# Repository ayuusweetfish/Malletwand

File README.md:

# Malletwand: the Pendulum as a Handheld Interface to Musical Timing

**Malletwand** is a handheld controller device in the form of a pendulum (a handle with a swinging bob), which can act as an input interface to the timing of musical playback.

We present this at [NIME](https://nime.org/) 2024 as a short paper ([PDF](paper/nime/paper.pdf); video to-be-updated) in paper session 10, on Friday, 6 Sep.

## Contents

The following directories contain all the files for design and implementation (hardware, firmware, and mechanical).
- **wand/**: the handheld controller (the "Wand").
  - Hardware is a single PCB; firmware for the two controllers are in subdirectories **fw/** (the main one) and **fw_bob/** (the small one in the bob/ball) respectively.
- **mallet/**: one unit of the self-playing (robotic) glockenspiel instrument (the "Mallet").
- **mallet_central/**: the central unit for the instrument, mostly managing communications (both wireless and wired).

To use the files, the following software packages are required (versions for reference):
- Hardware: KiCad (7.0.10)
- Firmware: Arm GNU Toolchain (GCC 10.3.1), STM32Cube ('G0 1.5.0, 'L0 1.12.1), PlatformIO (6.1.15)
- Mechanical: FreeCAD (0.21.1), OpenSCAD (2021.01)

The following directories contain miscellaneous resources:
- **numerical/**: Numerical experiments for the filtering algorithms (EKF and ALS), implemented in Julia.
- **paper/nime/**: The paper's LaTeX source and images.
- **testdrive/**: A testbed prototype for the sensors, created in the early days of development. Includes both hardware and firmware, and a desktop client to receive the BLE signals. Currently not well documented, but might be relevant for inspection (and visualisation?).
- **releases/**: Gerber files submitted to the PCB fabrication house.

## Licence
All content in this repository is distributed under CERN-OHL-S (CERN Open Hardware Licence Version 2, Strongly Reciprocal). See full text at **COPYING.txt** or [online](https://ohwr.org/cern_ohl_s_v2.txt).

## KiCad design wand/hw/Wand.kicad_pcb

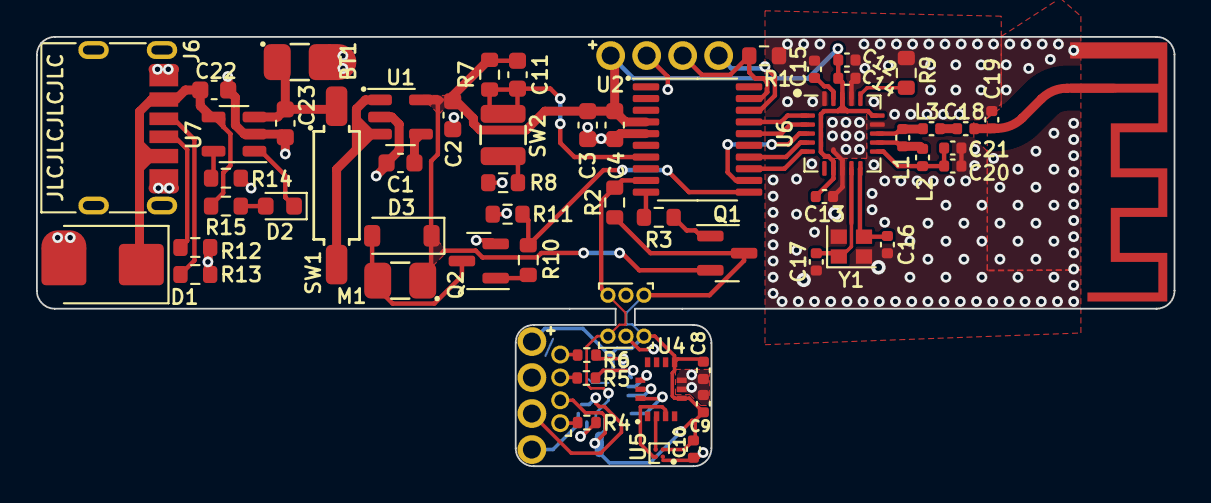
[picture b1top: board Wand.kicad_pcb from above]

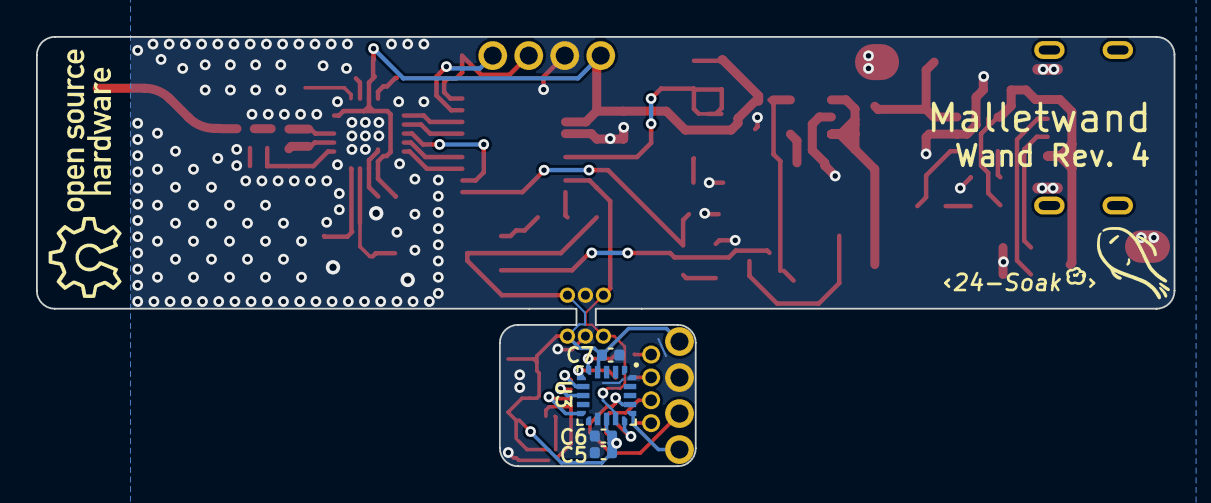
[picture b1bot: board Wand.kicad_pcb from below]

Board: 2 copper layers, 63.2 x 23.8 mm, 65 parts (4 on the bottom side), 49 nets.

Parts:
AE1: 2.4GHz 50R; ANT_IFA_USB_2.4GHz_50R
BT1: LiPo; Pads_1x02_P2.5
C1: 10n; C_0603_1608Metric
C2, C3, C22: 4.7u; C_0603_1608Metric
C4: 100n; C_0603_1608Metric
C5: 10u; C_0402_1005Metric
C6, C7, C8, C9: 100n; C_0402_1005Metric
C10: 2.2u; C_0402_1005Metric
C11: 1n; C_0603_1608Metric
C12: 4.7u; C_0402_1005Metric
C13, C14: 10n; C_0402_1005Metric
C15: 33n; C_0402_1005Metric
C16, C17: 10p; C_0402_1005Metric
C18: 1.5p; C_0402_1005Metric
C19: 1p; C_0402_1005Metric
C20: 2.2n; C_0402_1005Metric
C21: 4.7p; C_0402_1005Metric
C23: 10u; C_0603_1608Metric
D1: SMBJ5.0A; D_SMB
D2: LED; LED_0603_1608Metric
D3: MBR0530; D_SOD-123
J1, J4: Conn_01x04; TestPoints_1x04_P2.0
J2, J3: Conn_01x03; PinHeader_1x03_P1.00mm_Vertical
J5: Conn_01x04; PinHeader_1x04_P1.27mm_Vertical
J6: USB_C_Receptacle_PowerOnly_6P; USB_C_Receptacle
L1: 8.2n; C_0402_1005Metric
L2: 2.7n; C_0402_1005Metric
L3: 3.9n; C_0402_1005Metric
M1: Vib; Pads_1x02_P2.5
Q1: Si2301; SOT-23
Q2: Si2302; SOT-23
R1: 1.2M; R_0603_1608Metric
R2, R3, R10: 1k; R_0603_1608Metric
R4, R5, R6: 2k TBD; R_0402_1005Metric
R7: 3.3M; R_0603_1608Metric
R8, R11: 100k; R_0603_1608Metric
R9: 22k; R_0603_1608Metric
R12, R13: 5.1k; R_0603_1608Metric
R14: 2k; R_0603_1608Metric
R15: 6.8k; R_0603_1608Metric
SW1: SW_SPST; SPST_1x01_P2.54
SW2: Vib; VibSwitch_JYX-1210-X160
U1: SPX3819M5-L-3-3; SOT-23-5
U2: STM32G030F6Px; TSSOP-20_4.4x6.5mm_P0.65mm
U3: STM32L011F4Ux; ST_UFQFPN-20_3x3mm_P0.5mm
U4: BMI270; QFN50P300X250X87-14N
U5: MMC5603NJ; WLP-4_0.86x0.86mm_P0.4mm
U6: nRF24L01P; QFN-20-P0.5
U7: LTC4054ES5-4.2; TSOT-23-5
Y1: 16MHz; Crystal_SMD_2016-4Pin_2.0x1.6mm

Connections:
BMI_CS: U3.7 (PA4), U4.12 (CSB)
BMI_MOSI: U3.10 (PA7), U4.14 (SDX)
BMI_SCK: U3.8 (PA5), U4.13 (SCX)
BOB_DA: J2.3, J3.3, R2.1, U2.9 (PA2), U3.14 (PA9)
BSWCLK: J4.3, U3.17 (PA14)
BSWDIO: J4.4, U3.16 (PA13)
GND: AE1.2, BT1.2 (-), C1.2, C2.2, C3.2, C4.2, C5.2, C6.2, C7.2, C8.2, C9.2, C10.1, C12.2, C13.2, C14.2, C15.2, C16.2, C17.2, C19.2, C20.2, C21.2, C22.2, C23.2, D1.2 (A2), J1.2, J2.2, J3.2, J4.2, J6.A12 (GND), J6.B12 (GND), Q2.2 (S), R1.2, R8.1, R9.2, R11.1, R12.2, R13.2, R14.2, U1.2 (GND), U2.5 (VSS), U3.12 (VSS), U3.20 (PB9), U4.6 (GNDIO), U4.7 (GND), U5.A1 (VSA), U6.8 (VSS), U6.14 (VSS), U6.17 (VSS), U6.20 (VSS), U7.2 (GND), Y1.2, Y1.4
HSWCLK: J1.3, R1.1, U2.19 (PA14/PA15)
HSWDIO: J1.4, U2.18 (PA13)
LED_B: R6.2, U3.5 (PA0)
LED_G: R5.2, U3.6 (PA1)
LED_R: R4.2, U3.15 (PA10)
MOTOR_G: R10.1, R11.2, U2.11 (PA4)
unnamed: AE1.1, C18.2, C19.1
unnamed: C18.1, L3.2
unnamed: D2.2 (A), R15.2
unnamed: D2.1 (K), U7.1 (~CHRG)
unnamed: D3.2 (A), M1.2 (-), Q2.3 (D)
unnamed: J5.1, R4.1
unnamed: J5.3, R5.1
unnamed: J5.4, R6.1
unnamed: J6.A5 (CC1), R13.1
unnamed: J6.B5 (CC2), R12.1
unnamed: Q1.1 (G), R3.2
unnamed: Q2.1 (G), R10.2
unnamed: R8.2, SW2.1
unnamed: SW1.2 (B), U1.1 (IN), U1.3 (EN)
unnamed: C1.1, U1.4 (BP)
unnamed: U4.3 (ASCX), U5.A2 (SCL)
unnamed: U4.2 (ASDX), U5.B2 (SDA)
unnamed: L1.1, L2.1, U6.12 (ANT1)
unnamed: L1.2, L3.1, U6.13 (ANT2)
unnamed: C15.1, U6.19 (DVDD)
unnamed: R9.1, U6.16 (IREF)
unnamed: C20.1, C21.1, L2.2, U6.11 (VDD_PA)
unnamed: C16.1, U6.10 (XC1), Y1.3
unnamed: C17.1, U6.9 (XC2), Y1.1
unnamed: R14.1, U7.5 (PROG)
SUB_VDD_G: R3.1, U2.10 (PA3)
VBAT: BT1.1 (+), C23.1, SW1.1 (A), U7.3 (BAT)
VBUS: C22.1, D1.1 (A1), J6.A9 (VBUS), J6.B9 (VBUS), R15.1, U7.4 (V_{CC})
VDD: C2.1, C3.1, C4.1, C11.1, C12.1, C13.1, C14.1, D3.1 (K), J1.1, M1.1 (+), Q1.2 (S), R7.2, U1.5 (OUT), U2.4 (VDD), U6.7 (VDD), U6.15 (VDD), U6.18 (VDD)
VDDSUB: C5.1, C6.1, C7.1, C8.1, C9.1, C10.2, J2.1, J3.1, J4.1, J5.2, Q1.3 (D), R2.2, U3.4 (VDDA), U3.13 (VDD), U4.5 (VDDIO), U4.8 (VDD), U5.B1 (VDD)
VIB_TRG: C11.2, R7.1, SW2.2, U2.7 (PA0)
nRF_CE: U2.17 (PA12/PA10), U6.1 (CE)
nRF_CS: U2.16 (PA11/PA9), U6.2 (CSN)
nRF_MISO: U2.13 (PA6), U6.5 (MISO)
nRF_MOSI: U2.14 (PA7), U6.4 (MOSI)
nRF_SCK: U2.12 (PA5), U6.3 (SCK)

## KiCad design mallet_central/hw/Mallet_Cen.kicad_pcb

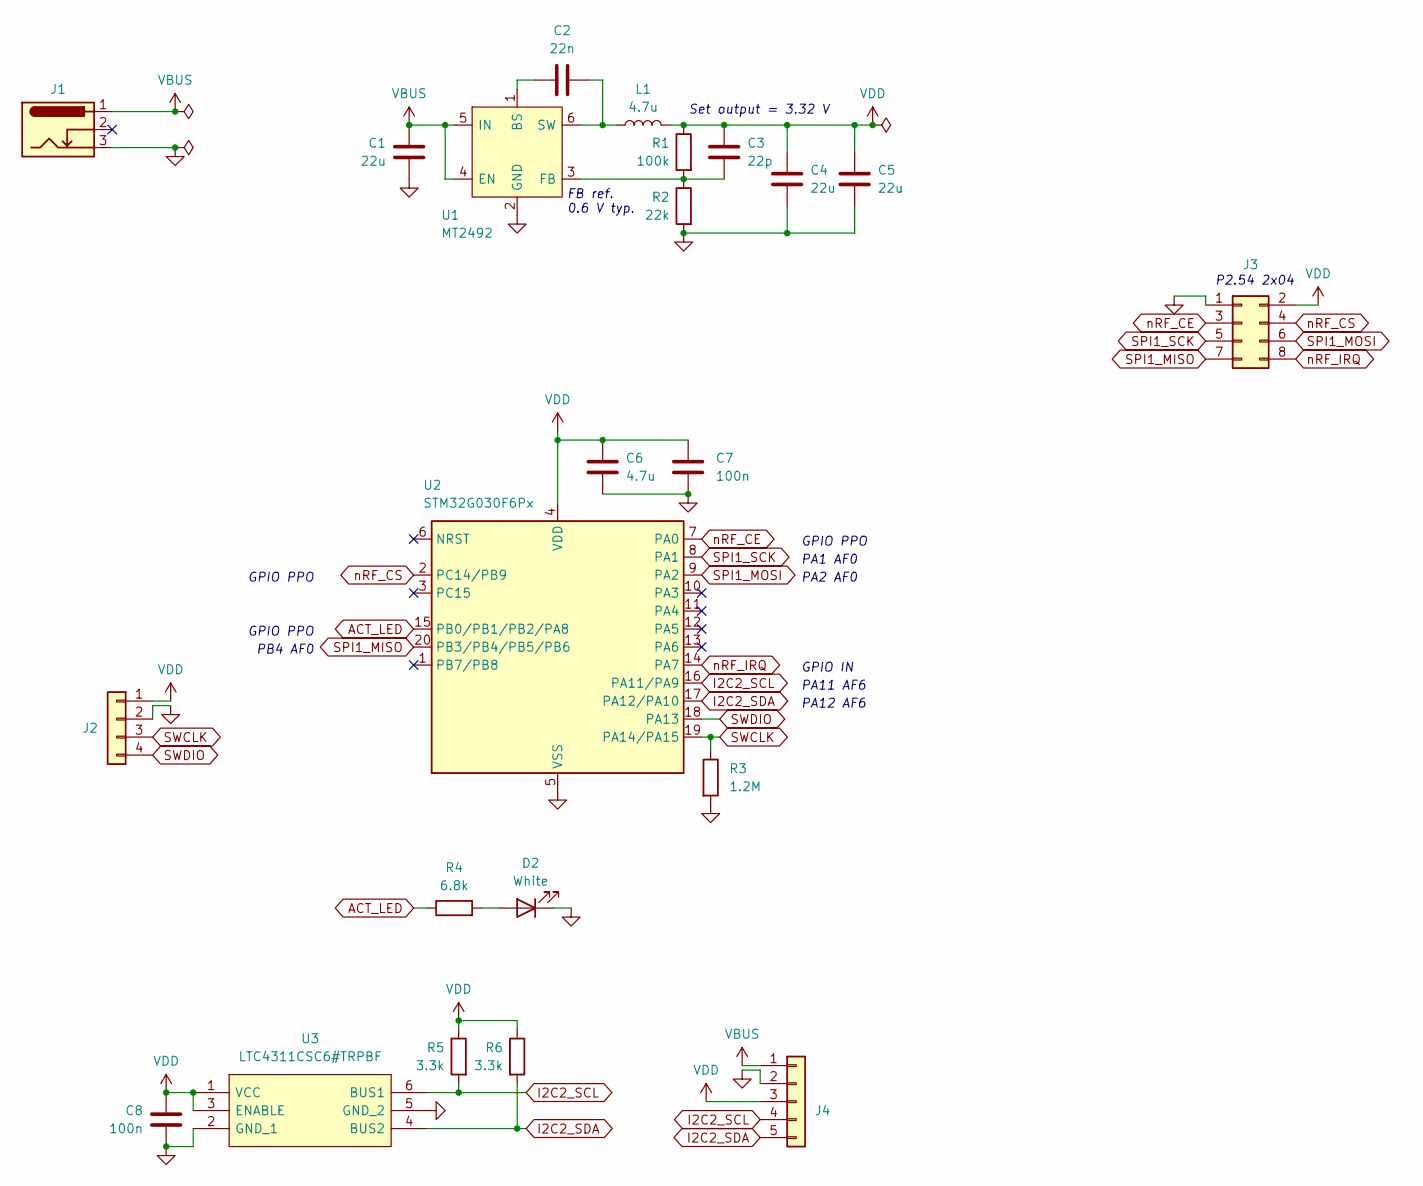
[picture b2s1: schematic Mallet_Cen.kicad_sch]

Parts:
C1, C4, C5: 22u; C_0603_1608Metric
C2: 22n; C_0603_1608Metric
C3: 22p; C_0603_1608Metric
C6: 4.7u; C_0603_1608Metric
C7, C8: 100n; C_0603_1608Metric
D2: White; LED_0603_1608Metric
J1: Barrel_Jack_Switch_Pin3Ring; BarrelJack_DC022
J2: Conn_01x04; TestPoints_1x04_P2.0
J3: Conn_02x04_Odd_Even; PinSocket_2x04_P2.54mm_Vertical
J4: Conn_01x05; PinHeader_1x05_P2.00mm_Vertical
L1: 4.7u; L_Sunlord_MWSA1004S
R1: 100k; R_0603_1608Metric
R2: 22k; R_0603_1608Metric
R3: 1.2M; R_0603_1608Metric
R4: 6.8k; R_0603_1608Metric
R5, R6: 3.3k; R_0603_1608Metric
U1: MT2492; SOT-23-6; Manufacturer_Part_Number MT2492
U2: STM32G030F6Px; TSSOP-20_4.4x6.5mm_P0.65mm
U3: LTC4311CSC6#TRPBF; SOT65P210X100-6N; Manufacturer_Part_Number LTC4311CSC6#TRPBF; Mouser Part Number 584-LTC4311CSC6TRPBF

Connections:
ACT_LED: R4.1, U2.15 (PB0/PB1/PB2/PA8)
GND: C1.2, C4.2, C5.2, C6.2, C7.2, C8.2, D2.1 (K), J1.3, J2.2, J3.1, J4.2, R2.2, R3.2, U1.2 (GND), U2.5 (VSS), U3.2 (GND_1), U3.5 (GND_2)
I2C2_SCL: J4.4, R5.2, U2.16 (PA11/PA9), U3.6 (BUS1)
I2C2_SDA: J4.5, R6.2, U2.17 (PA12/PA10), U3.4 (BUS2)
unnamed: D2.2 (A), R4.2
unnamed: C2.1, U1.1 (BS)
unnamed: C3.2, R1.2, R2.1, U1.3 (FB)
unnamed: C2.2, L1.1, U1.6 (SW)
SPI1_MISO: J3.7, U2.20 (PB3/PB4/PB5/PB6)
SPI1_MOSI: J3.6, U2.9 (PA2)
SPI1_SCK: J3.5, U2.8 (PA1)
SWCLK: J2.3, R3.1, U2.19 (PA14/PA15)
SWDIO: J2.4, U2.18 (PA13)
VBUS: C1.1, J1.1, J4.1, U1.4 (EN), U1.5 (IN)
VDD: C3.1, C4.1, C5.1, C6.1, C7.1, C8.1, J2.1, J3.2, J4.3, L1.2, R1.1, R5.1, R6.1, U2.4 (VDD), U3.1 (VCC), U3.3 (ENABLE)
nRF_CE: J3.3, U2.7 (PA0)
nRF_CS: J3.4, U2.2 (PC14/PB9)
nRF_IRQ: J3.8, U2.14 (PA7)

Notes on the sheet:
PA1 AF0
GPIO IN
PA11 AF6
PA2 AF0
GPIO PPO
Set output = 3.32 V
P2.54 2x04
PA12 AF6
PB4 AF0
FB ref. 0.6 V typ.

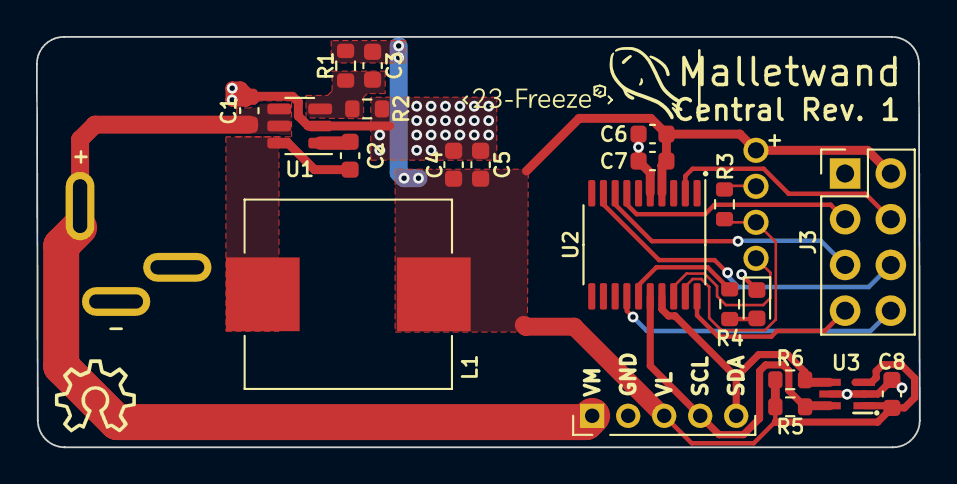
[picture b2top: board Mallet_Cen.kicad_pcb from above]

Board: 2 copper layers, 49.0 x 22.8 mm, 23 parts (0 on the bottom side), 18 nets.

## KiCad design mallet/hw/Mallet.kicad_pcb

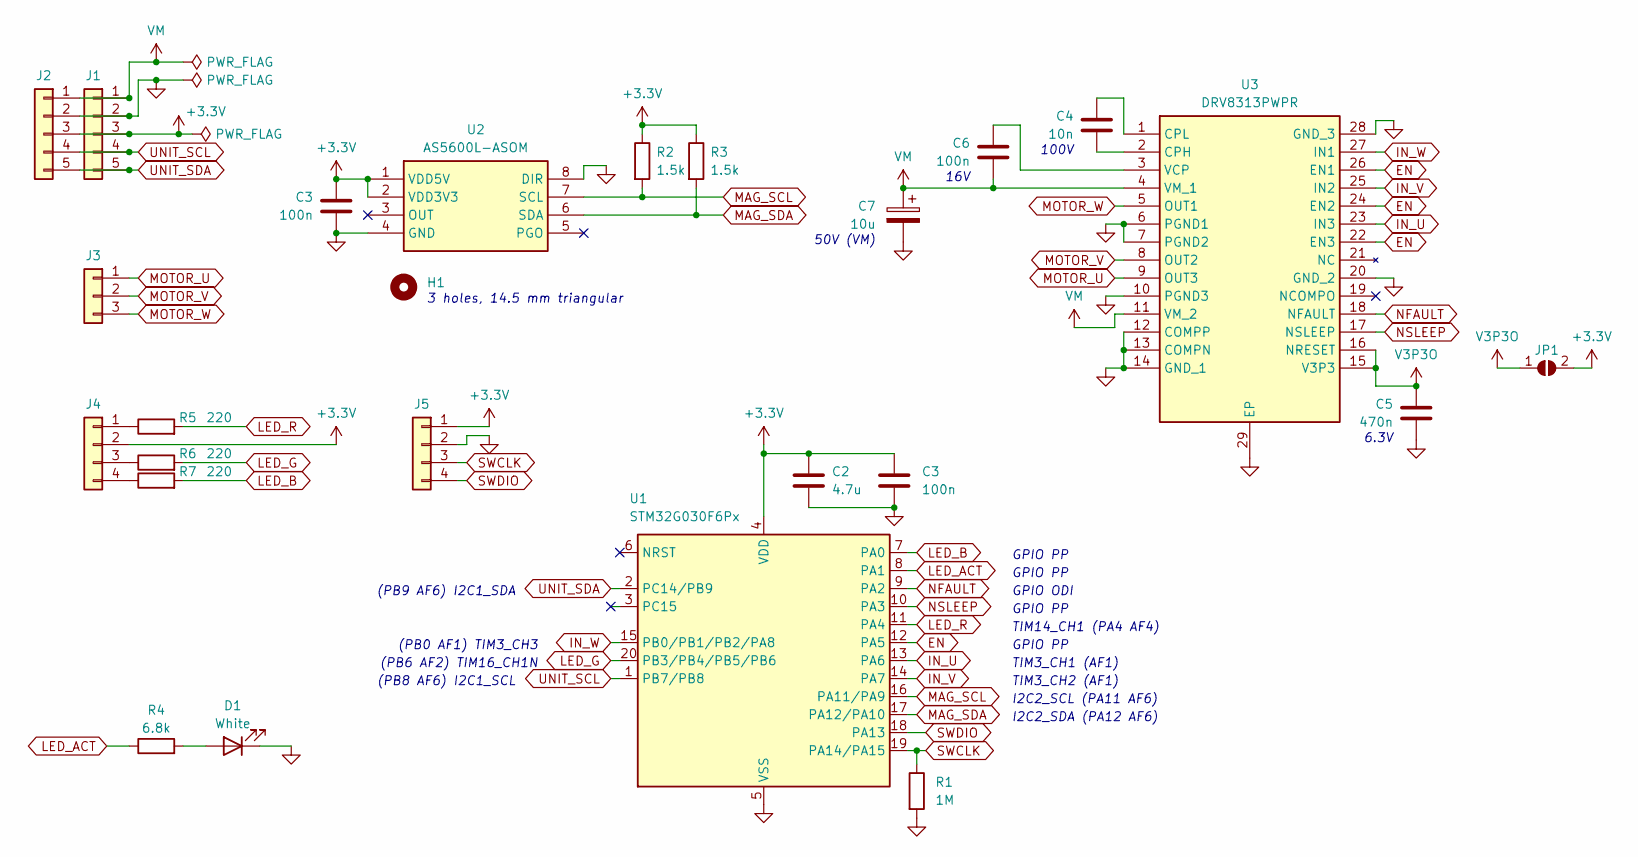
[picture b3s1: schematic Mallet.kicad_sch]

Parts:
C2: 4.7u; C_0603_1608Metric
C3, C6: 100n; C_0603_1608Metric
C4: 10n; C_0603_1608Metric
C5: 470n; C_0603_1608Metric
C7: 10u; CP_Elec_5x3.9
D1: White; LED_0603_1608Metric
H1: MountingHole; MountingHoles_M3_Tri14.5
J1, J2: Conn_01x05; PinHeader_1x05_P2.00mm_Vertical
J3: Conn_01x03; PinHeader_1x03_P2.00mm_Vertical
J4: Conn_01x04; PinHeader_1x04_P2.00mm_Vertical
J5: Conn_01x04; TestPoints_1x04_P2.0
JP1: SolderJumper_2_Open; SolderJumper-2_P1.3mm_Open_RoundedPad1.0x1.5mm
R1: 1M; R_0603_1608Metric
R2, R3: 1.5k; R_0603_1608Metric
R4: 6.8k; R_0603_1608Metric
R5, R6, R7: 220; R_0603_1608Metric
U1: STM32G030F6Px; TSSOP-20_4.4x6.5mm_P0.65mm
U2: AS5600L-ASOM; SOIC127P600X175-8N; Manufacturer_Part_Number AS5600L-ASOM; Mouser Part Number 985-AS5600L-ASOM
U3: DRV8313PWPR; SOP65P640X120-29N; Manufacturer_Part_Number DRV8313PWPR; Mouser Part Number 595-DRV8313PWPR

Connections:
+3.3V: C2.1, C3.1, J1.3, J2.3, J4.2, J5.1, JP1.2 (B), R2.1, R3.1, U1.4 (VDD), U2.1 (VDD5V), U2.2 (VDD3V3); also elsewhere on the board
EN: U1.12 (PA5), U3.22 (EN3), U3.24 (EN2), U3.26 (EN1)
GND: C2.2, C3.2, C5.2, C7.2, D1.1 (K), J1.2, J2.2, J5.2, R1.2, U1.5 (VSS), U2.4 (GND), U2.8 (DIR), U3.6 (PGND1), U3.7 (PGND2), U3.10 (PGND3), U3.12 (COMPP), U3.13 (COMPN), U3.14 (GND_1), U3.20 (GND_2), U3.28 (GND_3), U3.29 (EP); also elsewhere on the board
IN_U: U1.13 (PA6), U3.23 (IN3)
IN_V: U1.14 (PA7), U3.25 (IN2)
IN_W: U1.15 (PB0/PB1/PB2/PA8), U3.27 (IN1)
LED_ACT: R4.1, U1.8 (PA1)
LED_B: R7.2, U1.7 (PA0)
LED_G: R6.2, U1.20 (PB3/PB4/PB5/PB6)
LED_R: R5.2, U1.11 (PA4)
MAG_SCL: R2.2, U1.16 (PA11/PA9), U2.7 (SCL)
MAG_SDA: R3.2, U1.17 (PA12/PA10), U2.6 (SDA)
MOTOR_U: J3.1, U3.9 (OUT3)
MOTOR_V: J3.2, U3.8 (OUT2)
MOTOR_W: J3.3, U3.5 (OUT1)
NFAULT: U1.9 (PA2), U3.18 (NFAULT)
NSLEEP: U1.10 (PA3), U3.17 (NSLEEP)
unnamed: D1.2 (A), R4.2
unnamed: J4.1, R5.1
unnamed: J4.3, R6.1
unnamed: J4.4, R7.1
unnamed: C4.2, U3.2 (CPH)
unnamed: C4.1, U3.1 (CPL)
unnamed: C6.1, U3.3 (VCP)
SWCLK: J5.3, R1.1, U1.19 (PA14/PA15)
SWDIO: J5.4, U1.18 (PA13)
UNIT_SCL: J1.4, J2.4, U1.1 (PB7/PB8)
UNIT_SDA: J1.5, J2.5, U1.2 (PC14/PB9)
V3P3O: C5.1, JP1.1 (A), U3.15 (V3P3), U3.16 (NRESET)
VM: C6.2, C7.1, J1.1, J2.1, U3.4 (VM_1), U3.11 (VM_2)

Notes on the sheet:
GPIO PP
I2C2_SCL (PA11 AF6)
(PB8 AF6) I2C1_SCL
GPIO ODI
I2C2_SDA (PA12 AF6)
(PB0 AF1) TIM3_CH3
50V (VM)
16V
(PB9 AF6) I2C1_SDA
(PB6 AF2) TIM16_CH1N
100V
TIM3_CH1 (AF1)
TIM3_CH2 (AF1)
TIM14_CH1 (PA4 AF4)
6.3V
3 holes, 14.5 mm triangular

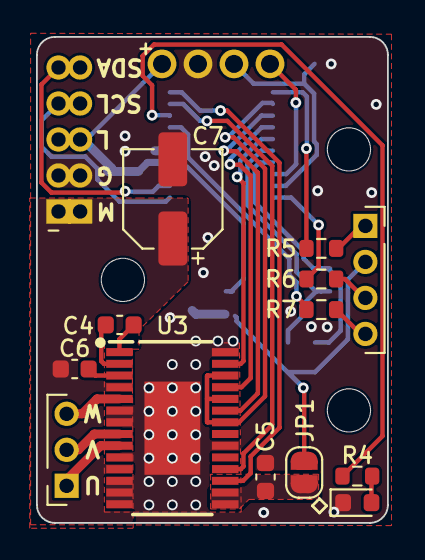
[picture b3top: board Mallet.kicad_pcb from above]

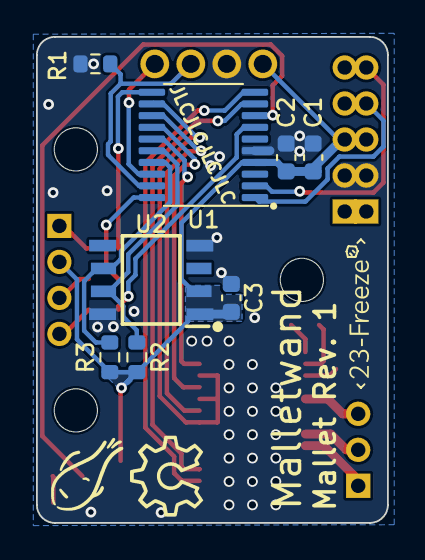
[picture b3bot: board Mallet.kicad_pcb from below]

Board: 2 copper layers, 19.5 x 27.0 mm, 25 parts (8 on the bottom side), 30 nets.

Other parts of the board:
C1: 4.7u; C_0603_1608Metric

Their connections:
+3.3V: C1.1; also elsewhere on the board
GND: C1.2; also elsewhere on the board

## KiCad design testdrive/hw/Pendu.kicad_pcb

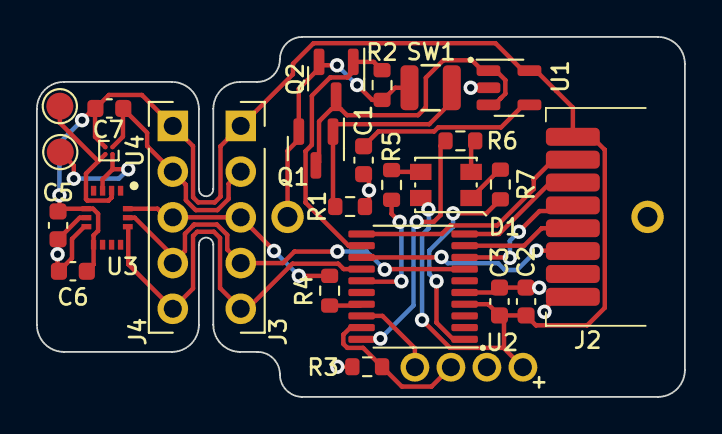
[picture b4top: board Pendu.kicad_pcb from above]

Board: 2 copper layers, 36.0 x 20.0 mm, 28 parts (1 on the bottom side), 26 nets.

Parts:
BT1: LIR2016; BatteryHolder_2032_THT_P20
C1: 10n; C_0603_1608Metric
C2: 4.7u; C_0603_1608Metric
C3, C5, C6: 100n; C_0603_1608Metric
C7: 2.2u; C_0603_1608Metric
D1: LED_RABG; LED_Kingbright_AAA3528ESGCT
J1: Conn_01x04; TestPoints_1x04_P2.0
J2: Conn_01x08; SMD_Module_P1.27_1x08
J3, J4: Conn_01x05; PinHeader_1x05_P2.54mm_Vertical
Q1, Q2: Si2301DS; SOT-23
R1, R2, R3: 1.2M; R_0603_1608Metric
R4: 1k; R_0603_1608Metric
R5, R6, R7: TBD; R_0603_1608Metric
SW1: Vib; VibSwitch_JYX-1210-X160
TP1, TP2: TestPoint; TestPoint_Pad_D1.5mm
U1: SPX3819M5-L-3-3; SOT-23-5
U2: STM32G030F6Px; TSSOP-20_4.4x6.5mm_P0.65mm
U3: BMI270; QFN50P300X250X87-14N
U4: MMC5603NJ; WLP-4_0.86x0.86mm_P0.4mm

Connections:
GND: BT1.2 (-), C1.2, C2.2, C3.2, C5.2, C6.2, C7.1, J1.2, J2.8, J3.2, J4.2, R1.2, R3.2, U1.2 (GND), U2.5 (VSS), U3.6 (GNDIO), U3.7 (GND), U4.A1 (VSA)
LED_B: R5.2, U2.15 (PB0/PB1/PB2/PA8)
LED_G: R6.2, U2.20 (PB3/PB4/PB5/PB6)
LED_R: R7.2, U2.1 (PB7/PB8)
unnamed: D1.3 (BK), R5.1
unnamed: D1.4 (GK), R6.1
unnamed: D1.1 (RK), R7.1
unnamed: Q1.3 (D), Q2.3 (D), U1.1 (IN), U1.3 (EN)
unnamed: Q1.1 (G), R1.1, SW1.1
unnamed: C1.1, U1.4 (BP)
unnamed: R4.1, U2.17 (PA12/PA10)
unnamed: TP1.1, U3.3 (ASCX), U4.A2 (SCL)
unnamed: TP2.1, U3.2 (ASDX), U4.B2 (SDA)
PWR_LATCH: Q2.1 (G), R2.2, U2.12 (PA5)
SPI1_CK: J2.4, U2.8 (PA1)
SPI1_CSx: J2.3, U2.10 (PA3)
SPI1_MISO: J2.6, U2.13 (PA6)
SPI1_MOSI: J2.5, U2.9 (PA2)
SPI2_CSx: J3.5, J4.5, U2.14 (PA7), U3.12 (CSB)
SPI2_MOSI: J3.3, J4.3, R4.2, U3.14 (SDX)
SPI2_SCK: J3.4, J4.4, U2.7 (PA0), U3.13 (SCX)
SWCLK: J1.3, R3.1, U2.19 (PA14/PA15)
SWDIO: J1.4, U2.18 (PA13)
VBAT: BT1.1 (+), Q1.2 (S), Q2.2 (S), R2.1, SW1.2
VDD: C2.1, C3.1, C5.1, C6.1, C7.2, D1.2 (A), J1.1, J2.1, J3.1, J4.1, U1.5 (OUT), U2.4 (VDD), U3.5 (VDDIO), U3.8 (VDD), U4.B1 (VDD)
nRF_CE: J2.2, U2.11 (PA4)

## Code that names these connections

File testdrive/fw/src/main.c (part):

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#include <stdio.h>
#include "../../cli/ekf.h"

#define PIN_PWR_LATCH   GPIO_PIN_5
#define PORT_PWR_LATCH  GPIOA

#define BMI_CS_PIN  GPIO_PIN_7
#define BMI_CS_PORT GPIOA
#define nRF_CS_PIN  GPIO_PIN_3
#define nRF_CS_PORT GPIOA
#define nRF_CE_PIN  GPIO_PIN_4
#define nRF_CE_PORT GPIOA

// #define RELEASE
#ifndef RELEASE
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static _release_inline uint8_t bmi270_read_reg(uint8_t reg)
{
  uint8_t data[2] = {0x80 | reg};
  HAL_GPIO_WritePin(BMI_CS_PORT, BMI_CS_PIN, 0);
  spi2_transmit(data, 1);
  spi2_receive(data, 2);
  HAL_GPIO_WritePin(BMI_CS_PORT, BMI_CS_PIN, 1);
  return data[1];
}
static _release_inline void bmi270_write_reg(uint8_t reg, uint8_t value)
{
  uint8_t data[2] = {reg, value};
  HAL_GPIO_WritePin(BMI_CS_PORT, BMI_CS_PIN, 0);
  spi2_transmit(data, 2);
  HAL_GPIO_WritePin(BMI_CS_PORT, BMI_CS_PIN, 1);
  // 2 µs delay
}
static _release_inline void bmi270_read_burst(uint8_t reg, uint8_t *data, uint32_t len)
{
  HAL_GPIO_WritePin(BMI_CS_PORT, BMI_CS_PIN, 0);
  uint8_t data_byte = {0x80 | reg};
  spi2_transmit(&data_byte, 1);
/*
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  static uint8_t buf[32];
  spi2_receive(buf, len + 1);
  for (int i = 0; i < len; i++) data[i] = buf[i + 1];
  HAL_GPIO_WritePin(BMI_CS_PORT, BMI_CS_PIN, 1);
}
static _release_inline void bmi270_write_burst(const uint8_t *data, uint32_t len)
{
  HAL_GPIO_WritePin(BMI_CS_PORT, BMI_CS_PIN, 0);
  spi2_transmit(data, len);
  HAL_GPIO_WritePin(BMI_CS_PORT, BMI_CS_PIN, 1);
}
static const uint8_t bmi270_config_file[] = {
  0x5E,
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
static _release_inline void nRF_send_len(const uint8_t *cmd, uint32_t size)
{
  HAL_GPIO_WritePin(nRF_CS_PORT, nRF_CS_PIN, GPIO_PIN_RESET);
  HAL_SPI_Transmit(&spi1, (uint8_t *)cmd, size, 1000);
  HAL_GPIO_WritePin(nRF_CS_PORT, nRF_CS_PIN, GPIO_PIN_SET);
}
#define nRF_send(...) do { \
  uint8_t buf[] = {__VA_ARGS__}; \
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  __HAL_RCC_GPIOB_CLK_ENABLE();
  GPIO_InitTypeDef gpio_init;

  // SWD (PA13, PA14)
  gpio_init.Pin = GPIO_PIN_13 | GPIO_PIN_14;
  gpio_init.Mode = GPIO_MODE_AF_PP; // Pass over control to AF peripheral
  gpio_init.Alternate = GPIO_AF0_SWJ;
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  gpio_init.Speed = GPIO_SPEED_FREQ_HIGH;
  HAL_GPIO_Init(GPIOA, &gpio_init);

  gpio_init.Pin = PIN_PWR_LATCH;
  gpio_init.Mode = GPIO_MODE_OUTPUT_OD;
  gpio_init.Pull = GPIO_NOPULL;
  gpio_init.Speed = GPIO_SPEED_FREQ_HIGH;
  HAL_GPIO_Init(PORT_PWR_LATCH, &gpio_init);
  HAL_GPIO_WritePin(PORT_PWR_LATCH, PIN_PWR_LATCH, GPIO_PIN_RESET);

  // ======== Clocks ========
  RCC_OscInitTypeDef osc_init = { 0 };
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  // APB1 = 16 MHz
  // period = 4 kHz = 4000 cycles

  // LED Blue, TIM14 Ch1, PB1
  gpio_init.Pin = GPIO_PIN_1;
  gpio_init.Mode = GPIO_MODE_AF_PP;
  gpio_init.Alternate = GPIO_AF0_TIM14;
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  HAL_TIM_PWM_ConfigChannel(&tim14, &tim14_ch1_oc_init, TIM_CHANNEL_1);
  HAL_TIM_PWM_Start(&tim14, TIM_CHANNEL_1);

  // LED Green, TIM16 Ch1N, PB6
  gpio_init.Pin = GPIO_PIN_6;
  gpio_init.Mode = GPIO_MODE_AF_PP;
  gpio_init.Alternate = GPIO_AF2_TIM16;
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  HAL_TIM_PWM_ConfigChannel(&tim16, &tim16_ch1_oc_init, TIM_CHANNEL_1);
  HAL_TIMEx_PWMN_Start(&tim16, TIM_CHANNEL_1);

  // LED Red, TIM17 Ch1N PB7
  gpio_init.Pin = GPIO_PIN_7;
  gpio_init.Mode = GPIO_MODE_AF_PP;
  gpio_init.Alternate = GPIO_AF2_TIM17;
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
  // ======== SPI ========
  // SPI1
  // SPI1_SCK (PA1 AF0), SPI1_MOSI (PA2 AF0), SPI1_MISO (PA6 AF0)
  gpio_init.Pin = GPIO_PIN_1 | GPIO_PIN_2 | GPIO_PIN_6;
  gpio_init.Mode = GPIO_MODE_AF_PP;
  gpio_init.Alternate = GPIO_AF0_SPI1;
  gpio_init.Pull = GPIO_NOPULL;
  gpio_init.Speed = GPIO_SPEED_FREQ_HIGH;
  HAL_GPIO_Init(GPIOA, &gpio_init);
  HAL_GPIO_WritePin(nRF_CS_PORT, nRF_CS_PIN, GPIO_PIN_SET);
  HAL_GPIO_WritePin(nRF_CE_PORT, nRF_CE_PIN, GPIO_PIN_RESET);
  HAL_Delay(10);

  __HAL_RCC_SPI1_CLK_ENABLE();
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  __HAL_SPI_ENABLE(&spi1);

  // nRF24L01+ CS, CE
  gpio_init.Pin = nRF_CS_PIN | nRF_CE_PIN;
  gpio_init.Mode = GPIO_MODE_OUTPUT_PP;
  gpio_init.Pull = GPIO_NOPULL;
  gpio_init.Speed = GPIO_SPEED_FREQ_HIGH;
  HAL_GPIO_Init(nRF_CS_PORT, &gpio_init);

  // Set up nRF24L01+
  nRF_send(0x20, 0x72); // CONFIG: Disable IRQ and CRC, power up
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    // TX_ADDR: Set transmit address

  // Read register 0x06 (RF_SETUP)
  HAL_GPIO_WritePin(nRF_CS_PORT, nRF_CS_PIN, GPIO_PIN_RESET);
  uint8_t spi_tx[2] = {0x06, 0x00};
  uint8_t spi_rx[2];
  HAL_SPI_TransmitReceive(&spi1, spi_tx, spi_rx, 2, 1000);
  HAL_GPIO_WritePin(nRF_CS_PORT, nRF_CS_PIN, GPIO_PIN_SET);
  if (spi_rx[0] != 0x0E || spi_rx[1] != 0x06) {
    // Error? Try a reset
    for (int i = 0; i < 11; i++) {
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  TIM14->CCR1 = 0;

  // SPI2
  // SPI2_SCK (PA0 AF0), SPI2_MOSI (PA10 AF0)
  gpio_init.Pin = GPIO_PIN_0 | GPIO_PIN_10;
  gpio_init.Mode = GPIO_MODE_AF_PP;
  gpio_init.Alternate = GPIO_AF0_SPI2;
  gpio_init.Pull = GPIO_NOPULL;
  gpio_init.Speed = GPIO_SPEED_FREQ_HIGH;
  HAL_GPIO_Init(GPIOA, &gpio_init);
  // Remap pin 17 (default PA12) to PA10
  __HAL_RCC_SYSCFG_CLK_ENABLE();
  SYSCFG->CFGR1 |= SYSCFG_REMAP_PA12;

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  __HAL_SPI_ENABLE(&spi2);

  // BMI270 CS
  gpio_init.Pin = BMI_CS_PIN;
  gpio_init.Mode = GPIO_MODE_OUTPUT_PP;
  gpio_init.Pull = GPIO_NOPULL;
  gpio_init.Speed = GPIO_SPEED_FREQ_HIGH;
  HAL_GPIO_Init(BMI_CS_PORT, &gpio_init);

  HAL_GPIO_WritePin(BMI_CS_PORT, BMI_CS_PIN, 0); HAL_Delay(1);
  HAL_GPIO_WritePin(BMI_CS_PORT, BMI_CS_PIN, 1); HAL_Delay(1);
  bmi270_read_reg(0x00);
  bmi270_write_reg(0x7E, 0xB6); // Soft reset
  HAL_Delay(1);

  HAL_GPIO_WritePin(BMI_CS_PORT, BMI_CS_PIN, 0); HAL_Delay(1);
  HAL_GPIO_WritePin(BMI_CS_PORT, BMI_CS_PIN, 1); HAL_Delay(1);
  bmi270_read_reg(0x00);
  bmi270_write_reg(0x6B, 0x01); // IF_CONF.spi3 = 1
  HAL_Delay(1);
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    nRF_send(0xE2); // FLUSH_RX
    nRF_cmd_buf[0] = 0xA0;  // W_TX_PAYLOAD
    nRF_send_len(nRF_cmd_buf, p + 4);
    HAL_GPIO_WritePin(nRF_CE_PORT, nRF_CE_PIN, GPIO_PIN_SET);
    return (struct proceed_t){tx_nRF_part_2, 2};
  }
  struct proceed_t tx_nRF_part_2() {
    HAL_GPIO_WritePin(nRF_CE_PORT, nRF_CE_PIN, GPIO_PIN_RESET);
    return (struct proceed_t){tx_nRF_part_1, 4};
  }

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
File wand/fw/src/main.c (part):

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#include "../../../testdrive/cli/geom.h"
#include "../../../testdrive/cli/elli_fit.h"

#define BMI_CS_PIN  GPIO_PIN_3
#define BMI_CS_PORT GPIOA
#define nRF_CS_PIN  GPIO_PIN_11
#define nRF_CS_PORT GPIOA
#define nRF_CE_PIN  GPIO_PIN_12
#define nRF_CE_PORT GPIOA
#define VDDSUB_G_PIN  GPIO_PIN_3
#define VDDSUB_G_PORT GPIOA
#define MOTOR_G_PIN   GPIO_PIN_4
#define MOTOR_G_PORT  GPIOA

// #define RELEASE
#ifndef RELEASE
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static _release_inline uint8_t bmi270_read_reg(uint8_t reg)
{
  uint8_t data[2] = {0x80 | reg};
  HAL_GPIO_WritePin(BMI_CS_PORT, BMI_CS_PIN, 0);
  spi2_transmit(data, 1);
  spi2_receive(data, 2);
  HAL_GPIO_WritePin(BMI_CS_PORT, BMI_CS_PIN, 1);
  return data[1];
}
static _release_inline void bmi270_write_reg(uint8_t reg, uint8_t value)
{
  uint8_t data[2] = {reg, value};
  HAL_GPIO_WritePin(BMI_CS_PORT, BMI_CS_PIN, 0);
  spi2_transmit(data, 2);
  HAL_GPIO_WritePin(BMI_CS_PORT, BMI_CS_PIN, 1);
  // 2 µs delay
}
static _release_inline void bmi270_read_burst(uint8_t reg, uint8_t *data, uint32_t len)
{
  HAL_GPIO_WritePin(BMI_CS_PORT, BMI_CS_PIN, 0);
  uint8_t data_byte = {0x80 | reg};
  spi2_transmit(&data_byte, 1);
/*
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  static uint8_t buf[32];
  spi2_receive(buf, len + 1);
  for (int i = 0; i < len; i++) data[i] = buf[i + 1];
  HAL_GPIO_WritePin(BMI_CS_PORT, BMI_CS_PIN, 1);
}
static _release_inline void bmi270_write_burst(const uint8_t *data, uint32_t len)
{
  HAL_GPIO_WritePin(BMI_CS_PORT, BMI_CS_PIN, 0);
  spi2_transmit(data, len);
  HAL_GPIO_WritePin(BMI_CS_PORT, BMI_CS_PIN, 1);
}
static const uint8_t bmi270_config_file[] = {
  0x5E,
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
static _release_inline void nRF_send_len(const uint8_t *cmd, uint32_t size)
{
  HAL_GPIO_WritePin(nRF_CS_PORT, nRF_CS_PIN, GPIO_PIN_RESET);
  HAL_SPI_Transmit(&spi1, (uint8_t *)cmd, size, 1000);
  HAL_GPIO_WritePin(nRF_CS_PORT, nRF_CS_PIN, GPIO_PIN_SET);
}
#define nRF_send(...) do { \
  uint8_t buf[] = {__VA_ARGS__}; \
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  __HAL_RCC_GPIOB_CLK_ENABLE();
  GPIO_InitTypeDef gpio_init;

  // SWD (PA13, PA14)
  gpio_init.Pin = GPIO_PIN_13 | GPIO_PIN_14;
  gpio_init.Mode = GPIO_MODE_AF_PP; // Pass over control to AF peripheral
  gpio_init.Alternate = GPIO_AF0_SWJ;
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  gpio_init.Mode = GPIO_MODE_OUTPUT_PP;
  HAL_GPIO_Init(VDDSUB_G_PORT, &gpio_init);
  HAL_GPIO_WritePin(VDDSUB_G_PORT, VDDSUB_G_PIN, 0);
  gpio_init.Pin = MOTOR_G_PIN;
  gpio_init.Mode = GPIO_MODE_OUTPUT_PP;
  HAL_GPIO_Init(MOTOR_G_PORT, &gpio_init);
  HAL_GPIO_WritePin(MOTOR_G_PORT, MOTOR_G_PIN, 0);

/*
  for (int i = 0; i < 4; i++) {
    HAL_Delay(500); HAL_GPIO_WritePin(MOTOR_G_PORT, MOTOR_G_PIN, 1);
    HAL_Delay(i < 2 ? 65 : 500); HAL_GPIO_WritePin(MOTOR_G_PORT, MOTOR_G_PIN, 0);
  }
*/
  HAL_Delay(50); HAL_GPIO_WritePin(MOTOR_G_PORT, MOTOR_G_PIN, 1);
  HAL_Delay(50); HAL_GPIO_WritePin(MOTOR_G_PORT, MOTOR_G_PIN, 0);

/*
  // FIXME: Rising edge corrupts program execution?
  bool parity = 0;
  while (1) {
    HAL_Delay(parity == 0 ? 1000 : 2000); HAL_GPIO_WritePin(VDDSUB_G_PORT, VDDSUB_G_PIN, parity ^= 1);
    // HAL_Delay(50); HAL_GPIO_WritePin(MOTOR_G_PORT, MOTOR_G_PIN, 1);
    // HAL_Delay(50); HAL_GPIO_WritePin(MOTOR_G_PORT, MOTOR_G_PIN, 0);
  }
*/

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if (1) {
  // ======== SPI ========
  // SPI1
  // SPI1_SCK (PA5 AF0), SPI1_MOSI (PA7 AF0), SPI1_MISO (PA6 AF0)
  gpio_init.Pin = GPIO_PIN_5 | GPIO_PIN_7 | GPIO_PIN_6;
  gpio_init.Mode = GPIO_MODE_AF_PP;
  gpio_init.Alternate = GPIO_AF0_SPI1;
  gpio_init.Pull = GPIO_NOPULL;
  gpio_init.Speed = GPIO_SPEED_FREQ_HIGH;
  HAL_GPIO_Init(GPIOA, &gpio_init);
  HAL_GPIO_WritePin(nRF_CS_PORT, nRF_CS_PIN, GPIO_PIN_SET);
  HAL_GPIO_WritePin(nRF_CE_PORT, nRF_CE_PIN, GPIO_PIN_RESET);
  HAL_Delay(10);

  __HAL_RCC_SPI1_CLK_ENABLE();
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  __HAL_SPI_ENABLE(&spi1);

  // nRF24L01+ CS, CE
  gpio_init.Pin = nRF_CS_PIN | nRF_CE_PIN;
  gpio_init.Mode = GPIO_MODE_OUTPUT_PP;
  gpio_init.Pull = GPIO_NOPULL;
  gpio_init.Speed = GPIO_SPEED_FREQ_HIGH;
  HAL_GPIO_Init(nRF_CS_PORT, &gpio_init);

  // Set up nRF24L01+
  nRF_send(0x20, 0x72); // CONFIG: Disable IRQ and CRC, power up
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
  // Read register 0x06 (RF_SETUP)
  for (int attempts = 1; attempts <= 5; attempts++) {
    HAL_GPIO_WritePin(nRF_CS_PORT, nRF_CS_PIN, GPIO_PIN_RESET);
    // Read registers STATUS (default first byte output) and RF_SETUP (0x06)
    uint8_t spi_tx[2] = {0x06, 0x00};
    uint8_t spi_rx[2];
    HAL_SPI_TransmitReceive(&spi1, spi_tx, spi_rx, 2, 1000);
    HAL_GPIO_WritePin(nRF_CS_PORT, nRF_CS_PIN, GPIO_PIN_SET);
    swv_printf("nRF24L01+ received status %02x %02x\n", spi_rx[0], spi_rx[1]);
    if (spi_rx[0] == 0x0E && spi_rx[1] == 0x06)
      break;
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}

  // ======== USART ========
  // USART2_TX (PA2 AF1)
  gpio_init = (GPIO_InitTypeDef){
    .Pin = GPIO_PIN_2,
    .Mode = GPIO_MODE_AF_OD,
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    nRF_send(0xE2); // FLUSH_RX
    nRF_cmd_buf[0] = 0xA0;  // W_TX_PAYLOAD
    nRF_send_len(nRF_cmd_buf, p + 4);
    HAL_GPIO_WritePin(nRF_CE_PORT, nRF_CE_PIN, GPIO_PIN_SET);
    return (struct proceed_t){tx_nRF_part_2, 2};
  }
  struct proceed_t tx_nRF_part_2() {
    HAL_GPIO_WritePin(nRF_CE_PORT, nRF_CE_PIN, GPIO_PIN_RESET);
    return (struct proceed_t){tx_nRF_part_1, 4};
  }

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
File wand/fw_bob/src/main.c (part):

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#include <stdint.h>
#include <stdio.h>

#define BMI_CS_PIN  GPIO_PIN_4
#define BMI_CS_PORT GPIOA

// #define RELEASE
#ifndef RELEASE
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static _release_inline uint8_t bmi270_read_reg(uint8_t reg)
{
  uint8_t data[2] = {0x80 | reg};
  HAL_GPIO_WritePin(BMI_CS_PORT, BMI_CS_PIN, 0);
  spi1_transmit(data, 1);
  spi1_receive(data, 2);
  HAL_GPIO_WritePin(BMI_CS_PORT, BMI_CS_PIN, 1);
  // swv_printf("read reg %02x: %02x %02x. error code %u\n", reg, data[0], data[1], spi1.ErrorCode);
  return data[1];
}
static _release_inline void bmi270_write_reg(uint8_t reg, uint8_t value)
{
  uint8_t data[2] = {reg, value};
  HAL_GPIO_WritePin(BMI_CS_PORT, BMI_CS_PIN, 0);
  spi1_transmit(data, 2);
  HAL_GPIO_WritePin(BMI_CS_PORT, BMI_CS_PIN, 1);
  // 2 µs delay
}
static _release_inline void bmi270_read_burst(uint8_t reg, uint8_t *data, uint32_t len)
{
  HAL_GPIO_WritePin(BMI_CS_PORT, BMI_CS_PIN, 0);
  uint8_t data_byte = {0x80 | reg};
  spi1_transmit(&data_byte, 1);

  static uint8_t buf[32];
  spi1_receive(buf, len + 1);
  for (int i = 0; i < len; i++) data[i] = buf[i + 1];
  HAL_GPIO_WritePin(BMI_CS_PORT, BMI_CS_PIN, 1);
}
static _release_inline void bmi270_write_burst(const uint8_t *data, uint32_t len)
{
  HAL_GPIO_WritePin(BMI_CS_PORT, BMI_CS_PIN, 0);
  spi1_transmit(data, len);
  HAL_GPIO_WritePin(BMI_CS_PORT, BMI_CS_PIN, 1);
}
static const uint8_t bmi270_config_file[] = {
  0x5E,
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  __HAL_RCC_GPIOB_CLK_ENABLE();
  GPIO_InitTypeDef gpio_init;

  // SWD (SWDIO PA13, SWCLK PA14)
  gpio_init.Pin = GPIO_PIN_13 | GPIO_PIN_14;
  gpio_init.Mode = GPIO_MODE_AF_PP; // Pass over control to AF peripheral
  gpio_init.Alternate = GPIO_AF0_SWDIO;
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  HAL_NVIC_SetPriority(SysTick_IRQn, 0, 0);

  // ======== USART ========
  // USART2_TX (PA9 AF4)
  gpio_init = (GPIO_InitTypeDef){
    .Pin = GPIO_PIN_9,
    .Mode = GPIO_MODE_AF_OD,
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
  // ======== SPI ========
  // SPI1
  // SPI1_SCK (PA5 AF0), SPI1_MOSI (PA7 AF0)
  gpio_init = (GPIO_InitTypeDef){
    .Pin = GPIO_PIN_5 | GPIO_PIN_7,
    .Mode = GPIO_MODE_AF_PP,
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    .Speed = GPIO_SPEED_FREQ_HIGH,
  };
  HAL_GPIO_Init(GPIOA, &gpio_init);
  // CS (PA4 GPIO)
  gpio_init = (GPIO_InitTypeDef){
    .Pin = BMI_CS_PIN,
    .Mode = GPIO_MODE_OUTPUT_PP,
    .Pull = GPIO_NOPULL,
    .Speed = GPIO_SPEED_FREQ_HIGH,
  };
  HAL_GPIO_Init(BMI_CS_PORT, &gpio_init);

  __HAL_RCC_SPI1_CLK_ENABLE();
  spi1 = (SPI_HandleTypeDef){
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
  // BMI270 set-up

  HAL_GPIO_WritePin(BMI_CS_PORT, BMI_CS_PIN, 0); HAL_Delay(1);
  HAL_GPIO_WritePin(BMI_CS_PORT, BMI_CS_PIN, 1); HAL_Delay(1);
  bmi270_read_reg(0x00);
  bmi270_write_reg(0x7E, 0xB6); // Soft reset
  HAL_Delay(1);

  HAL_GPIO_WritePin(BMI_CS_PORT, BMI_CS_PIN, 0); HAL_Delay(1);
  HAL_GPIO_WritePin(BMI_CS_PORT, BMI_CS_PIN, 1); HAL_Delay(1);
  bmi270_read_reg(0x00);
  bmi270_write_reg(0x6B, 0x01); // IF_CONF.spi3 = 1
  HAL_Delay(1);
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
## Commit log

2023-12-25 🎉 Create ECAD project for pendulum test drive
2023-12-26 Finish testdrive schematic
2023-12-26 Revise testdrive schematic, revert to unified VDD
2023-12-26 Finish PCB layout and routing (schematic fix to-do)
2023-12-27 Fix circuit design, submit for fabrication
2024-01-01 Add a glass ball holder 3D model
2024-01-05 Revise glass holder part
2024-01-08 Breathing lights
2024-01-08 Communicate with BMI270 through SPI
2024-01-08 Coloured lights by IMU data
2024-01-09 Add filter test
2024-01-09 Add fixed-point version of the filter
2024-01-10 Incorporate complementary filter into firmware
2024-01-10 Send BLE packets
2024-01-10 Implement multithreading
2024-01-13 Create schematic for updated wand hardware
2024-01-13 (WIP) Wand PCB design
2024-01-13 Revise wand hardware design
2024-01-13 Read data from magnetic sensor
2024-01-13 Continuously read from magnetic sensor
2024-01-14 Add numerical experiments for pendulum state estimation
2024-01-14 Minor optimization in experiment
2024-01-15 Revise silkscreen text; submit for fabrication
2024-01-15 Fix incorrect arctan-based phase estimation
2024-01-16 Add EKF numericla experiment
2024-01-17 Add flyback diode reminder
2024-01-17 Improve EKF
2024-01-18 Add key bar test model
2024-01-18 Revise EKF testing scheme
2024-01-18 Add spherical pendulum integrator
2024-01-19 Pass magnetometer data to client
2024-01-19 Visualise magnetometer and accelerometer values
2024-01-19 Minor tweaks
2024-01-19 Plot velocity of spherical pendulum
2024-01-19 Animate spherical pendulum
2024-01-19 Plot spherical integrations in small-angle cases
2024-01-20 Display all 9 axes
2024-01-20 Calibrate accelerometer w.r.t. gravity
2024-01-20 Add ellipsoid fitting implementation
2024-01-20 Port ellipsoid fitting to C
2024-01-20 Correctly fit the ellipsoid with the device
2024-01-21 Separate magnetometer calibration from accelerometer
2024-01-21 Complementary filter for orientation
2024-01-21 Correct x-y heading estimation with tilt angle
2024-01-21 (WIP) Print calibrated IMU readings?
2024-01-21 Estimate heading from gyroscope data with EKF
2024-01-21 Incorporate filtered heading into test client
2024-01-22 Test filter performance on hardware
2024-01-22 Properly identify ticks!
2024-01-22 Properly visualise filtered phase output
2024-01-22 Fix incorrect markings in ECAD files
2024-01-22 Run firmware on the wand hardware (Wand Rev. 2)
2024-01-22 Add mallet schematic
2024-01-23 Finish mallet PCB
2024-01-23 Add mallet central hardware design
2024-01-23 Revise central module hardware design
2024-01-23 Revise central module PCB for JLCPCB QR code
2024-01-23 Fix incorrect pin assignment for external RF module; submit for fab
2024-01-24 Optimise EKF subroutine
2024-01-25 Enable VDDSUB in program
2024-01-25 Activate vibration motor
2024-01-25 Blink LED with all three channels
2024-01-26 Migrate to G031F8
2024-01-26 Pull down motor NMOS gate for stable booting
2024-01-27 Revise wand PCB as per fab. clearance requirements
2024-01-30 Run firware on mallet units
2024-01-30 Add lost unoptimised EKF header
2024-01-30 Fix firmware; start rotating
2024-01-30 Add firmware for the central unit, blinking LED
2024-01-30 Add mallet holder part design
2024-01-30 Clean up ellipsoid fitting subroutine
2024-01-30 (WIP) Correct filtering in the firmware
2024-01-31 Add metal bars mechanical design; submit for fab
2024-01-31 Tune EKF on device
2024-01-31 Automatic gravity calibration and further filter tuning
2024-01-31 Alternating colours on beats
2024-01-31 Clean up unit firmware
2024-01-31 Functional I2C communication
2024-02-01 Beat extrapolator
2024-02-01 Revise mechanical parts for mallet unit
2024-02-01 Weighted least squares for beat extrapolation
2024-02-01 Minimal data transmission and minimal client
2024-02-01 Improved filter again
2024-02-01 Calibrate motor
2024-02-01 Emulate the movement of a stroke (no sound yet)
2024-02-01 (WIP) Better strokes
2024-02-02 Add testing option in firmware
2024-02-02 Retry nRF24L01+ communication on startup errors
2024-02-02 Improved strokes
2024-02-02 Save power by reducing torque when idle
2024-02-03 Revise rebounce control
2024-02-03 Revise testrun behvaiour (blink fast on I2C error)
2024-02-03 Add demo video script
2024-02-04 Revise mallet holder mechanical parts, again
2024-02-04 Emulate PWM for LED blue channel
2024-02-04 Fix emulated PWM cannot reach 0% duty
2024-02-04 Improve consistency of emulated PWM IRQ subroutine
2024-02-04 Blink LED on stroke
2024-02-04 Revise strokes
2024-02-04 Light up and wait before starting!
2024-02-04 Add player colour in the wand
2024-02-05 Auto-play tune
2024-02-05 Auto-play on wand; increase wand LED brightness
2024-02-05 Misc. changes for demonstration
2024-02-06 Add paper template
2024-02-06 (WIP) Paper, introduction and related work
2024-02-07 (WIP) Paper (intro & related work)
2024-02-07 (WIP) Paper
2024-02-08 (WIP?) Paper
2024-02-08 Paper
2024-02-08 Minor fixes
2024-04-09 Test program memory usage on STM32L011
2024-04-26 🚧 Revise schematic; use a separate MCU for the bob
2024-04-26 Finish revision of schematic
2024-04-26 🚧 Updating circuit board design
2024-04-29 Finish wand board update
2024-04-30 Finishing touches of board revision; submit for fab
2024-05-07 Add wand casing CAD model
2024-05-08 🚧 Revise firmware
2024-05-08 🎉 Revise paper 📸
2024-05-09 Is this perfectionism, or is this just 🍊🥤🌊
2024-07-16 🚧 Mark possible places for corrections in firmware
2024-07-17 Fix bob firmware
2024-07-17 Add a few more notes
2024-08-02 🚧 Attempts at communicating with SPI devices (defect unknown)
2024-08-02 🚧 UART correctly receives, but data is incorrect?
2024-08-02 🚧 Still
2024-08-03 Correctly receiving UART signals
2024-08-03 🚧 Bidirectional UART?
2024-08-03 Resolve issues with SPI
2024-08-03 Read-outs from IMU
2024-08-07 Working bidirectional UART communication
2024-08-07 Implement minimal `vsnprintf` to reduce ROM footprint
2024-08-07 Reduce ROM footprint of UART subroutines
2024-08-07 Send sensor data from the 'L0 to the 'G0
2024-08-07 Receive and broadcast sensor data!
2024-08-07 Replace BMI270 configuration with a minimal version
2024-09-03 Document a bit
2024-09-03 Revise docs; remove redundant files
2026-01-21 Move NIME paper to dedicated directory
2026-01-21 Add CHI EA article template
2026-01-21 Add bibliography
2026-01-21 Add floor plan (?)
2026-01-21 Video subtitles...
2026-01-22 Revise introduction and copy remaining NIME content
2026-01-22 Edit article
2026-01-22 Fix typos
2026-01-23 Add missing symlink
